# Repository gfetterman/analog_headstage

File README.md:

# Analog Headstage

Eagle design file for a simple 7 channel analog headstage

## Bill of Materials
Connectors:

+ 1x OMNETICS PZN-12-AA

Op-amps:

+ 2x TI TL074CPWR

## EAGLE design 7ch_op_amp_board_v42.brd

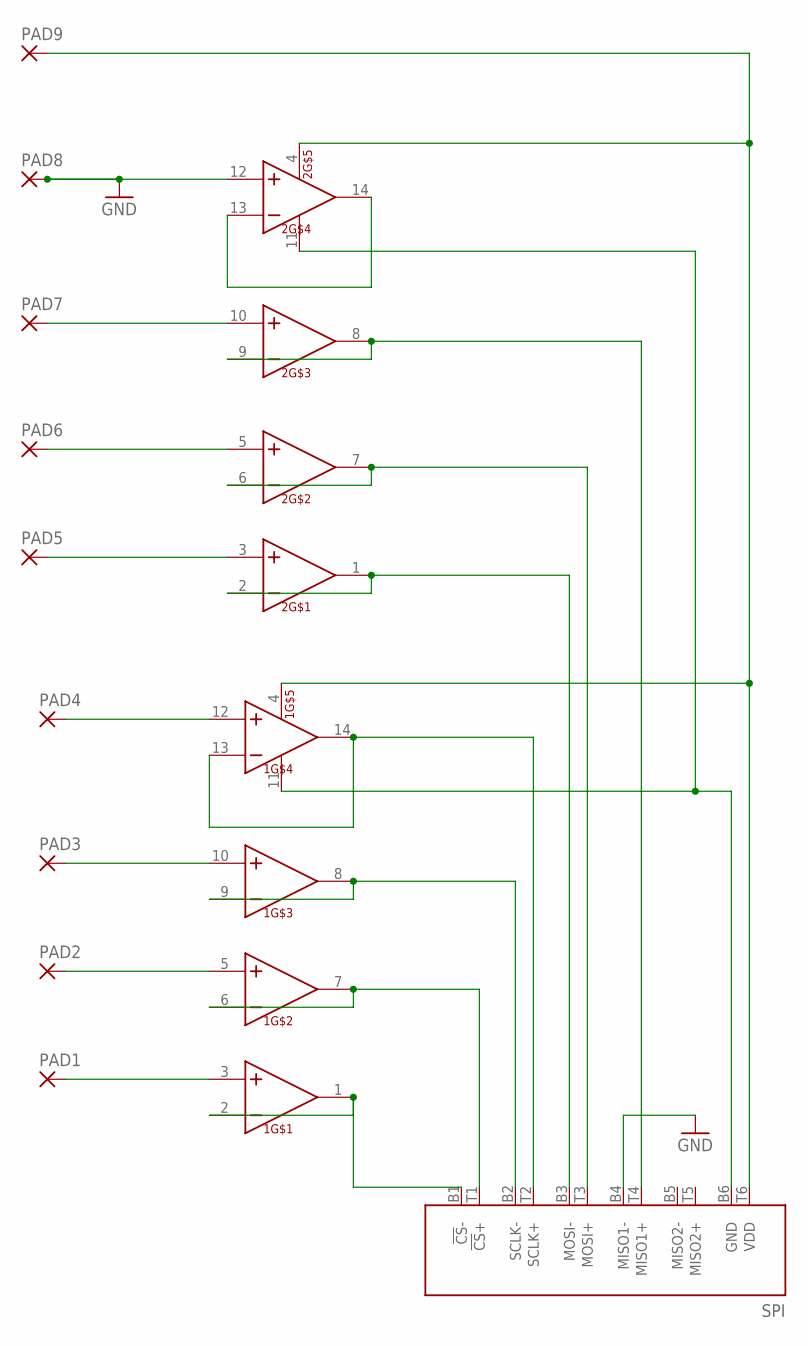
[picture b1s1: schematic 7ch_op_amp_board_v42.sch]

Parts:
1, 2: TL074-TSSOP; TSSOP14
PAD1, PAD2, PAD3, PAD4, PAD5, PAD6, PAD7, PAD8, PAD9: 1,6/0,9
SPI: RHD2000-CABLE-AMP-SIDE; OMNETICS_PZN-12-AA

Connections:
GND: 2.12 (IN+), PAD8.1, SPI.B4 (MISO1-)
unnamed: 1.1 (OUT), 1.2 (IN-), SPI.B1 (!CS!-)
unnamed: 1.6 (IN-), 1.7 (OUT), SPI.T1 (!CS!+)
unnamed: 2.1 (OUT), 2.2 (IN-), SPI.B3 (MOSI-)
unnamed: 2.6 (IN-), 2.7 (OUT), SPI.T3 (MOSI+)
unnamed: 2.8 (OUT), 2.9 (IN-), SPI.T4 (MISO1+)
unnamed: 2.13 (IN-), 2.14 (OUT)
unnamed: 1.13 (IN-), 1.14 (OUT), SPI.T2 (SCLK+)
unnamed: 1.3 (IN+), PAD1.1
unnamed: 1.8 (OUT), 1.9 (IN-), SPI.B2 (SCLK-)
unnamed: 1.5 (IN+), PAD2.1
unnamed: 1.10 (IN+), PAD3.1
unnamed: 1.12 (IN+), PAD4.1
unnamed: 2.10 (IN+), PAD7.1
unnamed: 2.5 (IN+), PAD6.1
unnamed: 2.3 (IN+), PAD5.1
V+: 1.4 (VCC+), 2.4 (VCC+), PAD9.1, SPI.T6 (VDD)
V-: 1.11 (VCC-), 2.11 (VCC-), SPI.B6 (GND)

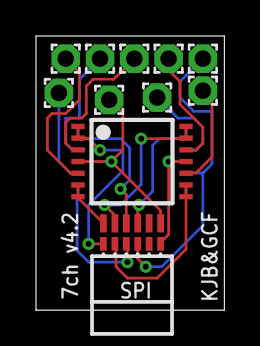
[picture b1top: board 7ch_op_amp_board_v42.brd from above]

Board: 2 copper layers, 10.5 x 15.2 mm, 12 parts (1 on the bottom side), 18 nets.

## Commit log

2017-02-28 Replace connector with through-holes
2017-02-28 Update bill of materials
2017-03-03 Add through-hole for V+
2017-03-04 Redraw traces to isolate power
2017-03-04 Simplify routing
2017-03-04 Cleanup files
2017-03-04 Update version in silkscreen
